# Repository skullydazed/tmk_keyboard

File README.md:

NOTICE: This repository is obsolete!
====================================

Please use my fork of QMK in the future: <https://github.com/skullydazed/qmk_firmware>

TMK Keyboard Firmware Collection
================================
This is a keyboard firmware with some useful features for Atmel AVR controller.

Source code is available here: <http://github.com/tmk/tmk_keyboard>

Updates
-------
#### 2015/04/22
Core library was separated to other branch `core`. <https://github.com/tmk/tmk_keyboard/tree/core>

In `Makefile` you need to set `TMK_DIR` to indicate core library location now.

    TMK_DIR = ../../tmk_core

Features
--------
These features can be used in your keyboard.

* Multi-layer Keymap  - Multiple keyboard layouts with layer switching
* Mouse key           - Mouse control with keyboard
* System Control Key  - Power Down, Sleep, Wake Up and USB Remote Wake up
* Media Control Key   - Volume Down/Up, Mute, Next/Prev track, Play, Stop and etc
* USB NKRO            - 120 keys(+ 8 modifiers) simultaneously
* PS/2 mouse support  - PS/2 mouse(TrackPoint) as composite device
* Keyboard protocols  - PS/2, ADB, M0110, Sun and other old keyboard protocols
* User Function       - Customizable function of key with writing code
* Macro               - Very primitive at this time
* Keyboard Tricks     - Oneshot modifier and modifier with tapping feature
* Debug Console       - Messages for debug and interaction with firmware
* Virtual DIP Switch  - Configurations stored EEPROM(Boot Magic)
* Locking CapsLock    - Mechanical switch support for CapsLock
* Breathing Sleep LED - Sleep indicator with charm during USB suspend
* Backlight           - Control backlight levels

Projects
--------
You can find some keyboard specific projects under `converter` and `keyboard` directory.

### converter
* [ps2_usb](converter/ps2_usb/)             - [PS/2 keyboard to USB][GH_ps2]
* [adb_usb](converter/adb_usb/)             - [ADB keyboard to USB][GH_adb]
* [m0110_usb](converter/m0110_usb)          - [Macintosh 128K/512K/Plus keyboard to USB][GH_m0110]
* [terminal_usb](converter/terminal_usb/)   - [IBM Model M terminal keyboard(PS/2 scancode set3) to USB][GH_terminal]
* [news_usb](converter/news_usb/)           - [Sony NEWS keyboard to USB][GH_news]
* [x68k_usb](converter/x68k_usb/)           - [Sharp X68000 keyboard to USB][GH_x68k]
* [sun_usb](converter/sun_usb/)             - [Sun] to USB(type4, 5 and 3?)
* [pc98_usb](converter/pc98_usb/)           - [PC98] to USB
* [usb_usb](converter/usb_usb/)             - USB to USB(experimental)
* [ascii_usb](converter/ascii_usb/)         - ASCII(Serial console terminal) to USB
* [ibm4704_usb](converter/ibm4704_usb)      - [IBM 4704 keyboard Converter][GH_ibm4704]

### keyboard
* [hhkb](keyboard/hhkb/)                    - [Happy Hacking Keyboard pro][GH_hhkb] **my main board**
* [gh60](keyboard/gh60/)                    - [GH60] DIY 60% keyboard [prototype][GH60_proto] **my second board**
* [hbkb](keyboard/hbkb/)                    - [Happy Buckling spring keyboard][GH_hbkb](IBM Model M 60% mod)
* [hid_liber](keyboard/hid_liber/)          - [HID liberation][HID_liber] controller (by alaricljs)
* [phantom](keyboard/phantom/)              - [Phantom] keyboard (by Tranquilite)
* [IIgs_Standard](keyboard/IIgs/)           - Apple [IIGS] keyboard mod(by JeffreySung)
* [macway](keyboard/macway/)                - [Compact keyboard mod][GH_macway] [retired]
* [KMAC](keyboard/kmac/)                    - Korean custom keyboard
* [Lightsaber](keyboard/lightsaber/)        - Korean custom keyboard
* [Infinity](keyboard/infinity/)            - Massdrop [Infinity keyboard][Infinity]
* [NerD](keyboard/nerd/)                    - Korean custom keyboard
* [KittenPaw](keyboard/kitten_paw)          - Custom Majestouch controller
* [Lightpad](keyboard/lightpad)             - Korean custom keypad
* [ghost_squid](keyboard/ghost_squid/)      - [The Ghost Squid][ghost_squid] controller for [Cooler Master QuickFire XT][cmxt]

### Extenal projects using tmk_keyboard
* [ErgoDox_cub-uanic][cub-uanic]            - Split Ergonomic Keyboard [ErgoDox][ergodox_org]
* [mcdox][mcdox_tmk]                        - [mcdox][mcdox]

[GH_macway]:    http://geekhack.org/showwiki.php?title=Island:11930
[GH_hhkb]:      http://geekhack.org/showwiki.php?title=Island:12047
[GH_ps2]:       http://geekhack.org/showwiki.php?title=Island:14618
[GH_adb]:       http://geekhack.org/showwiki.php?title=Island:14290
[GH_hhkb_bt]:   http://geekhack.org/showwiki.php?title=Island:20851
[GH_m0110]:     http://geekhack.org/showwiki.php?title=Island:24965
[GH_news]:      http://geekhack.org/showwiki.php?title=Island:25759
[GH_terminal]:  http://geekhack.org/showwiki.php?title=Island:27272
[GH_x68k]:      http://geekhack.org/showwiki.php?title=Island:29060
[GH_hbkb]:      http://geekhack.org/showwiki.php?title=Island:29483
[GH_ibm4704]:   http://geekhack.org/index.php?topic=54706.0
[HID_liber]:    http://deskthority.net/wiki/HID_Liberation_Device_-_DIY_Instructions
[Phantom]:      http://geekhack.org/index.php?topic=26742
[GH60]:         http://geekhack.org/index.php?topic=34959
[GH60_proto]:   http://geekhack.org/index.php?topic=37570.0
[PC98]:         http://en.wikipedia.org/wiki/NEC_PC-9801
[Sun]:          http://en.wikipedia.org/wiki/Sun-3
[IIGS]:         http://en.wikipedia.org/wiki/Apple_IIGS
[Infinity]:     https://www.massdrop.com/buy/infinity-keyboard-kit
[ghost_squid]:  http://deskthority.net/wiki/Costar_replacement_controllers#The_Ghost_Squid
[cmxt]:         http://gaming.coolermaster.com/en/products/keyboards/quickfirext/
[ergodox_org]:  http://ergodox.org/
[cub-uanic]:    https://github.com/cub-uanic/tmk_keyboard/tree/master/keyboard/ergodox
[mcdox]:        https://github.com/DavidMcEwan/mcdox
[mcdox_tmk]:    https://github.com/DavidMcEwan/tmk_keyboard/tree/master/keyboard/mcdox

License
-------
**GPLv2** or later. Some protocol files are under **Modified BSD License**.

Third party libraries like LUFA, PJRC and V-USB have their own license respectively.

Build Firmware and Program Controller
-------------------------------------
See [doc/build.md](doc/build.md).

Change your keymap
------------------
See [doc/keymap.md](doc/keymap.md).

Magic Commands
--------------
To see help press `Magic` + `H`.

`Magic` key combination is `LShift` + `RShift` in many project, but `Power` key on ADB converter. 
`Magic` keybind can be vary on each project, check `config.h` in project directory.

Following commands can be also executed with `Magic` + key. In console mode `Magic` keybind is not needed.

    ----- Command Help -----
    c:      enter console mode
    d:      toggle debug enable
    x:      toggle matrix debug
    k:      toggle keyboard debug
    m:      toggle mouse debug
    v:      print device version & info
    t:      print timer count
    s:      print status
    e:	    print eeprom config
    n:	    toggle NKRO
    0/F10:  switch to Layer0
    1/F1:   switch to Layer1
    2/F2:   switch to Layer2
    3/F3:   switch to Layer3
    4/F4:   switch to Layer4
    PScr:   power down/remote wake-up
    Caps:   Lock Keyboard(Child Proof)
    Paus:   jump to bootloader

Boot Magic Configuration - Virtual DIP Switch
---------------------------------------------
Boot Magic are executed during boot up time. Press Magic key below then plug in keyboard cable.
Note that you must use keys of **Layer 0** as Magic keys. These settings are stored in EEPROM so that retain your configure over power cycles.

To avoid configuring accidentally additive salt key `KC_SPACE` also needs to be pressed along with the following configuration keys. The salt key is configurable in `config.h`. See [tmk_core/common/bootmagic.h](tmk_core/common/bootmagic.h).

#### General
- Skip reading EEPROM to start with default configuration(`ESC`)
- Clear configuration stored in EEPROM to reset configuration(`Backspace`)

#### Bootloader
- Kick up Bootloader(`B`)

#### Debug
- Debug enable(`D`)
- Debug matrix enable(`D`+`X`)
- Debug keyboard enable(`D`+`K`)
- Debug mouse enable(`D`+`M`)

#### Keymap
- Swap Control and CapsLock(`Left Control`)
- Change CapsLock to Control(`Caps Lock`)
- Swap LeftAlt and Gui(`Left Alt`)
- Swap RightAlt and Gui(`Right Alt`)
- Disable Gui(`Left Gui`)
- Swap Grave and Escape(`Grave`)
- Swap BackSlash and BackSpace(`Back Slash`)
- Enable NKRO on boot(`N`)

#### Default Layer
- Set Default Layer to 0(`0`)
- Set Default Layer to 1(`1`)
- Set Default Layer to 2(`2`)
- Set Default Layer to 3(`3`)
- Set Default Layer to 4(`4`)
- Set Default Layer to 5(`5`)
- Set Default Layer to 6(`6`)
- Set Default Layer to 7(`7`)

Mechanical Locking support
--------------------------
This feature makes it possible for you to use mechanical locking switch for `CapsLock`, `NumLock` 
or `ScrollLock`. To enable this feature define these macros in `config.h` and use `KC_LCAP`, `KC_LN
UM` or `KC_LSCR` in keymap for locking key instead of normal `KC_CAPS`, `KC_NLCK` or `KC_SLCK`. Res
ync option tries to keep switch state consistent with keyboard LED state.
 
    #define LOCKING_SUPPORT_ENABLE
    #define LOCKING_RESYNC_ENABLE

Start Your Own Project
-----------------------
**TBD**

Debugging
--------
Use PJRC's `hid_listen` to see debug messages. You can use the tool for debug even if firmware use LUFA stack.

You can use xprintf() to display debug info on `hid_listen`, see `tmk_core/common/xprintf.h`.

Files and Directories
-------------------
### Top
* tmk_core/     - core library
* keyboard/     - keyboard projects
* converter/    - protocol converter projects
* doc/          - documents

Coding Style
-------------
- Doesn't use Tab to indent, use 4-spaces instead.

Other Keyboard Firmware Projects
------------------
You can learn a lot about keyboard firmware from these. See [doc/other_projects.md](doc/other_projects.md).

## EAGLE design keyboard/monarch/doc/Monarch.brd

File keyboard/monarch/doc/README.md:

Monarch keyboard firmware
=========================
DIY compact keyboard designed by koalapear, PCB designed by skullY.

## Monarch Resources
- [GeekHack Thread](https://geekhack.org/index.php?topic=75786.0)

## LED Support

After routing the matrix the Monarch had 2 pins left over. This allows for controllable lighting for two of the LED's. There are 3 possible LED's to turn on:

* Underlighting
* Capslock
* Numlock

There are two configurations available out of the box. You can switch between them by setting or commenting out the BACKLIGHT_ENABLE line in the Makefile. You must comment it out to disable it, changing it to NO will not work.

### Underlighting

To add underlighting to your Monarch you will need to solder on 16 SMD LED's and 16 matched resistors. For the LED's you can use anything from 0805 to 1206. If you have questions about whether your chosen LED/resistor combo will work post on the geekhack thread. Once you have added the components you will need to wire up the LED's.

There are 3 possible ways to wire underlighting:

* Always On
* Physical toggle switch
* Controllable brightness

To have your underlighting always on solder a jumper between GND and UNDERLIGHT, and another one between the FET bypass. This is the simplest way to enable underlighting.

If you would like to be able to turn off your underlighting, wire a physical toggle switch between the two contacts at the FET bypass.

To have controllable brightness connect C6 to UNDERLIGHT, and add a MOSFET and 10K resistor to the pads on the board. Make sure that the FET bypass is not connected. With BACKLIGHT_ENABLE set in the Makefile you can press Fn+Numlock to cycle through brightness levels.

### Capslock and Numlock

By default the firmware assumes you have CAPSLOCK wired to B6. If you have commented out BACKLIGHT_ENABLE it will assume that NUMLOCK is connected to C6. You can change this in [led.c](led.c).

## Build
Move to this directory then just run `make` like:

    $ make

## Keymap
Several version of keymap are available in advance but you are recommended to define your favorite layout yourself. To define your own keymap create file named `keymap_<name>.c` and see keymap document(you can find in top README.md) and existent keymap files.

To build firmware binary hex file with a certain keymap just do `make` with `KEYMAP` option like:

    $ make KEYMAP=[default|<name>]

### 1  default
[keymap_default.c](keymap_default.c) Default monarch layout

#### 1.0 Default ANSI layer
    FIXME

#### 1.1 Default Fn Layer
    FIXME

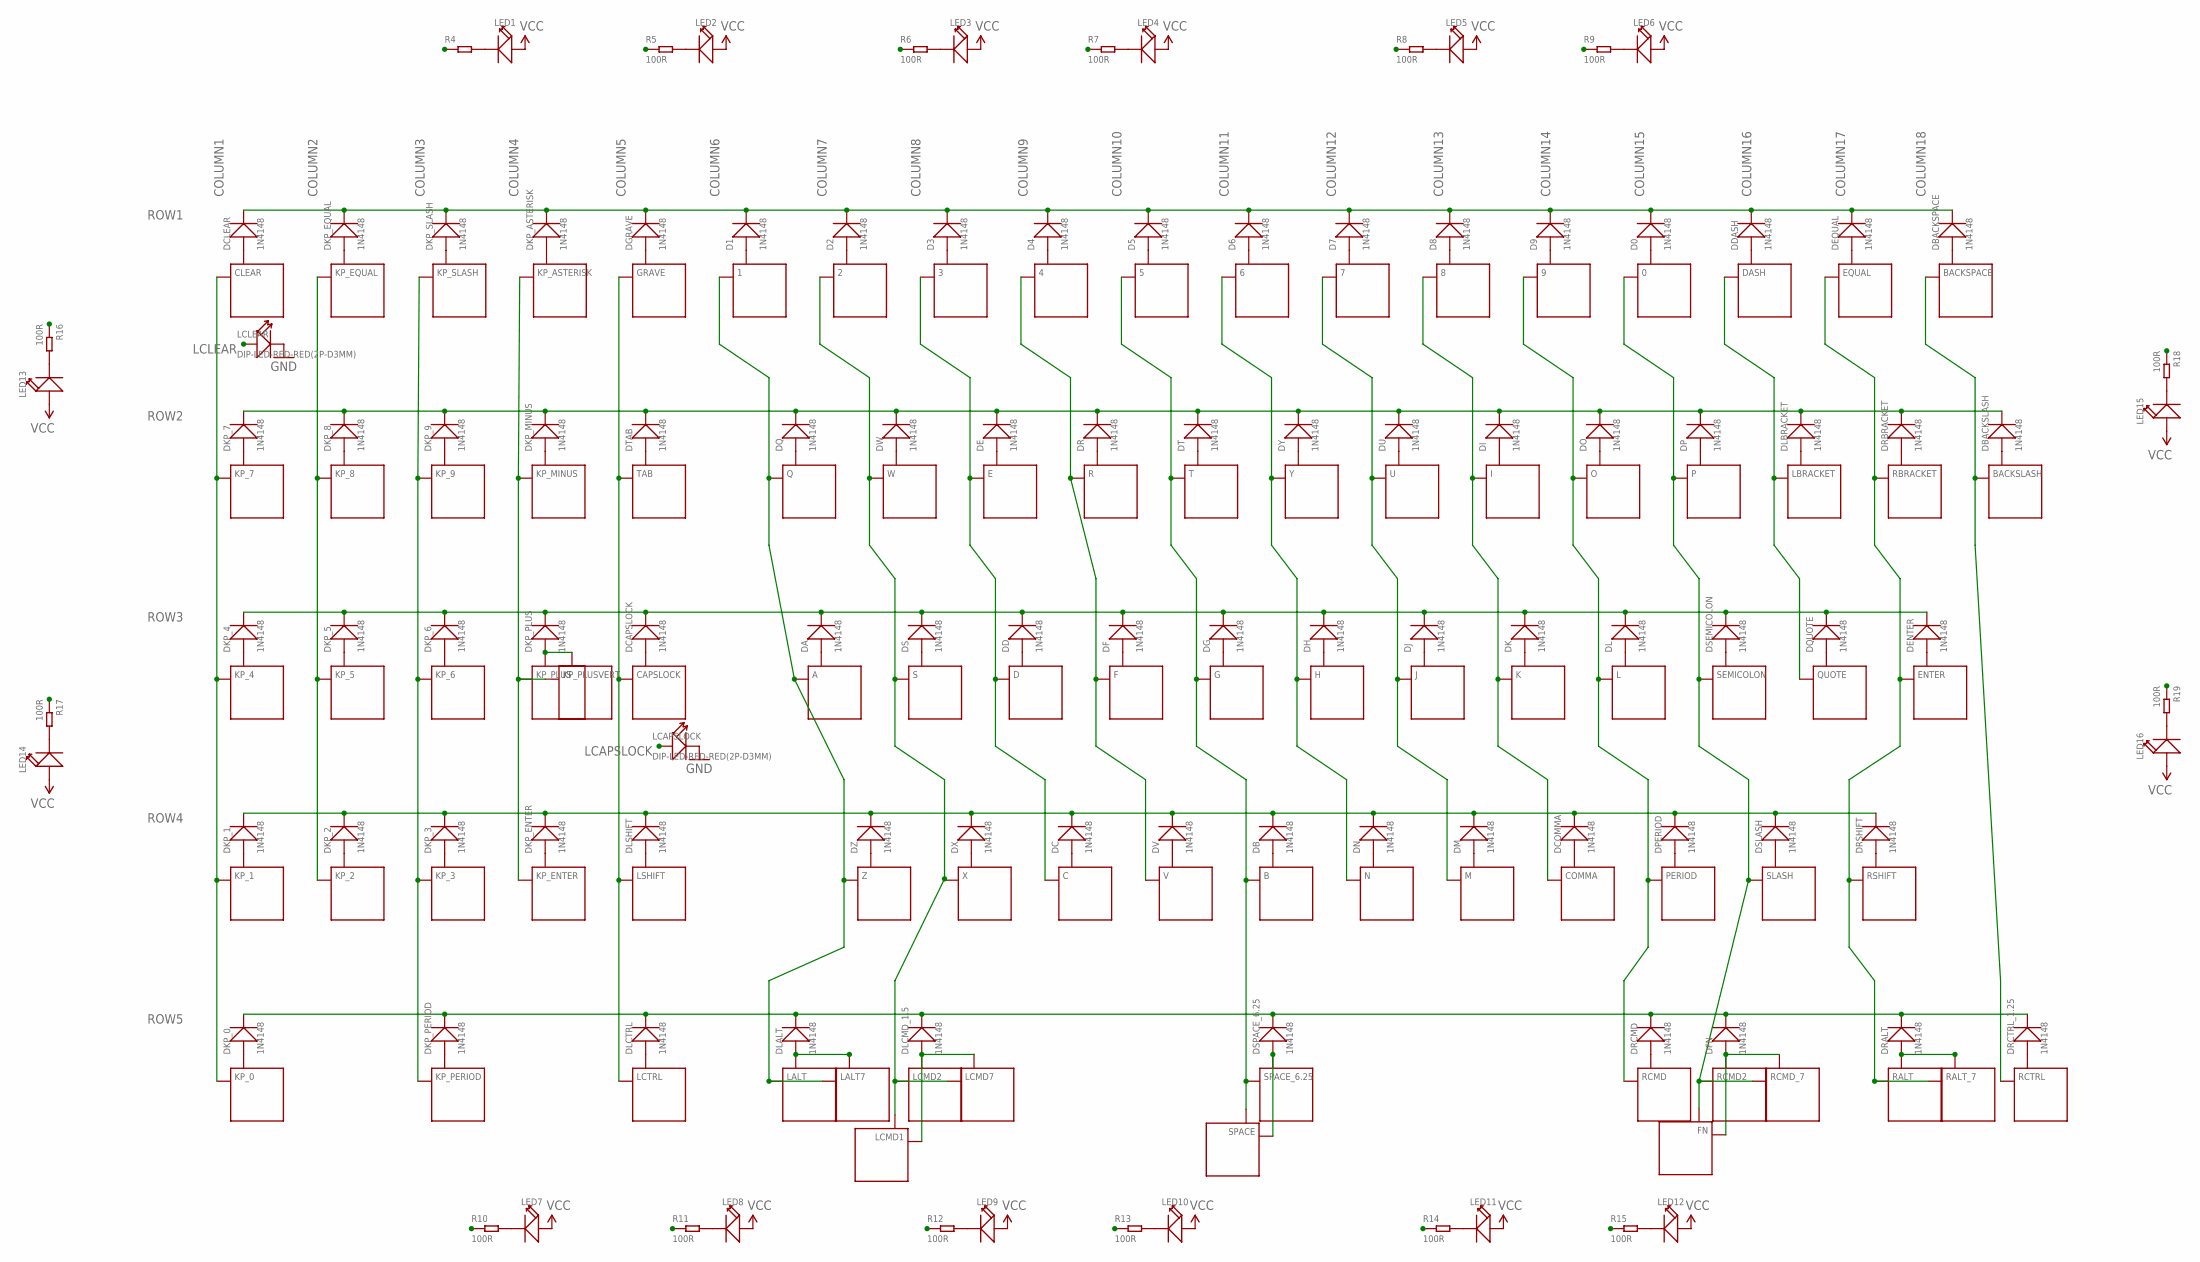
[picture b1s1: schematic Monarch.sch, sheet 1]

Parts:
0, 1, 2, 3, 4, 5, 6, 7, 8, 9: ALPS; P-ALPS
A: ALPS; P-ALPS
B: ALPS; P-ALPS
BACKSLASH: ALPS; P-ALPS
BACKSPACE: ALPS; P-ALPS
C: ALPS; P-ALPS
CAPSLOCK: ALPS; P-ALPS
CLEAR: ALPS; P-ALPS
COMMA: ALPS; P-ALPS
D: ALPS; P-ALPS
D0, D1, D2, D3, D4, D5, D6, D7, D8, D9: 1N4148; SOD-123
DA: 1N4148; SOD-123
DASH: ALPS; P-ALPS
DB: 1N4148; SOD-123
DBACKSLASH: 1N4148; SOD-123
DBACKSPACE: 1N4148; SOD-123
DC: 1N4148; SOD-123
DCAPSLOCK: 1N4148; SOD-123
DCLEAR: 1N4148; SOD-123
DCOMMA: 1N4148; SOD-123
DD: 1N4148; SOD-123
DDASH: 1N4148; SOD-123
DE: 1N4148; SOD-123
DENTER: 1N4148; SOD-123
DEQUAL: 1N4148; SOD-123
DF: 1N4148; SOD-123
DFN: 1N4148; SOD-123
DG: 1N4148; SOD-123
DGRAVE: 1N4148; SOD-123
DH: 1N4148; SOD-123
DI: 1N4148; SOD-123
DJ: 1N4148; SOD-123
DK: 1N4148; SOD-123
DKP_0, DKP_1, DKP_2, DKP_3, DKP_4, DKP_5, DKP_6, DKP_7, DKP_8, DKP_9: 1N4148; SOD-123
DKP_ASTERISK: 1N4148; SOD-123
DKP_ENTER: 1N4148; SOD-123
DKP_EQUAL: 1N4148; SOD-123
DKP_MINUS: 1N4148; SOD-123
DKP_PERIOD: 1N4148; SOD-123
DKP_PLUS: 1N4148; SOD-123
DKP_SLASH: 1N4148; SOD-123
DL: 1N4148; SOD-123
DLALT: 1N4148; SOD-123
DLBRACKET: 1N4148; SOD-123
DLCMD_1.5: 1N4148; SOD-123
DLCTRL: 1N4148; SOD-123
DLSHIFT: 1N4148; SOD-123
DM: 1N4148; SOD-123
DN: 1N4148; SOD-123
DO: 1N4148; SOD-123
DP: 1N4148; SOD-123
DPERIOD: 1N4148; SOD-123
DQ: 1N4148; SOD-123
DQUOTE: 1N4148; SOD-123
DR: 1N4148; SOD-123
DRALT: 1N4148; SOD-123
DRBRACKET: 1N4148; SOD-123
DRCMD: 1N4148; SOD-123
DRCTRL_1.25: 1N4148; SOD-123
DRSHIFT: 1N4148; SOD-123
DS: 1N4148; SOD-123
DSEMICOLON: 1N4148; SOD-123
DSLASH: 1N4148; SOD-123
DSPACE_6.25: 1N4148; SOD-123
DT: 1N4148; SOD-123
DTAB: 1N4148; SOD-123
DU: 1N4148; SOD-123
DV: 1N4148; SOD-123
DW: 1N4148; SOD-123
DX: 1N4148; SOD-123
DY: 1N4148; SOD-123
DZ: 1N4148; SOD-123
E: ALPS; P-ALPS
ENTER: ALPS; P-ALPS
EQUAL: ALPS; P-ALPS
F: ALPS; P-ALPS
FN: ALPS; P-ALPS
G: ALPS; P-ALPS
GRAVE: ALPS; P-ALPS
H: ALPS; P-ALPS
I: ALPS; P-ALPS
J: ALPS; P-ALPS
K: ALPS; P-ALPS
KP_0, KP_1, KP_2, KP_3, KP_4, KP_5, KP_6, KP_7, KP_8, KP_9: ALPS; P-ALPS
KP_ASTERISK: ALPS; P-ALPS
KP_ENTER: ALPS; P-ALPS
KP_EQUAL: ALPS; P-ALPS
KP_MINUS: ALPS; P-ALPS
KP_PERIOD: ALPS; P-ALPS
KP_PLUS: ALPS; P-ALPS
KP_PLUSVERT: ALPS; P-ALPS
KP_SLASH: ALPS; P-ALPS
L: ALPS; P-ALPS
LALT: ALPS-2SWITCH-0.5; P-ALPS-2SWITCH-0.5
LALT7: ALPS; P-ALPS
LBRACKET: ALPS; P-ALPS
LCAPSLOCK: DIP-LED-RED-RED(2P-D3MM); LED2-2.54-D3.0MM
LCLEAR: DIP-LED-RED-RED(2P-D3MM); LED2-2.54-D3.0MM
LCMD1, LCMD2, LCMD7: ALPS; P-ALPS
LCTRL: ALPS-2SWITCH-0.25; P-ALPS-2SWITCH-0.25
LED1, LED2, LED3, LED4, LED5, LED6, LED7, LED8, LED9, LED10, LED11, LED12, LED13, LED14, LED15, LED16: SMD-LED-GENERIC; P-SMD-LED-GENERIC
LSHIFT: ALPS; P-ALPS
M: ALPS; P-ALPS
N: ALPS; P-ALPS
O: ALPS; P-ALPS
P: ALPS; P-ALPS
PERIOD: ALPS; P-ALPS
Q: ALPS; P-ALPS
QUOTE: ALPS; P-ALPS
R: ALPS; P-ALPS
R4: SMD-RES-100R-5%-1/8W(0805); R0805
R5, R6, R7, R8, R9, R10, R11, R12, R13, R14, R15, R16, R17, R18, R19: 100R; R0805
RALT: ALPS-2SWITCH-0.5; P-ALPS-2SWITCH-0.5
RALT_7: ALPS; P-ALPS
RBRACKET: ALPS; P-ALPS
RCMD, RCMD2: ALPS; P-ALPS
RCMD_7: ALPS; P-ALPS
RCTRL: ALPS-2SWITCH-0.25; P-ALPS-2SWITCH-0.25
RSHIFT: ALPS; P-ALPS
S: ALPS; P-ALPS
SEMICOLON: ALPS; P-ALPS
SLASH: ALPS; P-ALPS
SPACE: ALPS; P-ALPS
SPACE_6.25: ALPS; P-ALPS
T: ALPS; P-ALPS
TAB: ALPS; P-ALPS
U: ALPS; P-ALPS
V: ALPS; P-ALPS
W: ALPS; P-ALPS
X: ALPS; P-ALPS
Y: ALPS; P-ALPS
Z: ALPS; P-ALPS

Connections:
COLUMN1: CLEAR.ALPS1, KP_0.ALPS1, KP_1.ALPS1, KP_4.ALPS1, KP_7.ALPS1; also elsewhere on the board
COLUMN2: KP_2.ALPS1, KP_5.ALPS1, KP_8.ALPS1, KP_EQUAL.ALPS1; also elsewhere on the board
COLUMN3: KP_3.ALPS1, KP_6.ALPS1, KP_9.ALPS1, KP_PERIOD.ALPS1, KP_SLASH.ALPS1; also elsewhere on the board
COLUMN4: KP_ASTERISK.ALPS1, KP_ENTER.ALPS1, KP_MINUS.ALPS1, KP_PLUS.ALPS1, KP_PLUSVERT.ALPS1; also elsewhere on the board
COLUMN5: CAPSLOCK.ALPS1, GRAVE.ALPS1, LCTRL.ALPS1, LCTRL.ALPS3, LSHIFT.ALPS1, TAB.ALPS1; also elsewhere on the board
COLUMN6: 1.ALPS1, A.ALPS1, LALT.ALPS1, LALT.ALPS4, LALT7.ALPS1, Q.ALPS1, Z.ALPS1; also elsewhere on the board
COLUMN7: 2.ALPS1, LCMD1.ALPS2, LCMD2.ALPS1, LCMD7.ALPS1, S.ALPS1, W.ALPS1, X.ALPS1; also elsewhere on the board
COLUMN8: 3.ALPS1, C.ALPS1, D.ALPS1, E.ALPS1; also elsewhere on the board
COLUMN9: 4.ALPS1, F.ALPS1, R.ALPS1, V.ALPS1; also elsewhere on the board
COLUMN10: 5.ALPS1, B.ALPS1, G.ALPS1, SPACE.ALPS2, SPACE_6.25.ALPS1, T.ALPS1; also elsewhere on the board
COLUMN11: 6.ALPS1, H.ALPS1, N.ALPS1, Y.ALPS1; also elsewhere on the board
COLUMN12: 7.ALPS1, J.ALPS1, M.ALPS1, U.ALPS1; also elsewhere on the board
COLUMN13: 8.ALPS1, COMMA.ALPS1, I.ALPS1, K.ALPS1; also elsewhere on the board
COLUMN14: 9.ALPS1, L.ALPS1, O.ALPS1, PERIOD.ALPS1, RCMD.ALPS1; also elsewhere on the board
COLUMN15: 0.ALPS1, FN.ALPS2, P.ALPS1, RCMD2.ALPS1, RCMD_7.ALPS1, SEMICOLON.ALPS1, SLASH.ALPS1; also elsewhere on the board
COLUMN16: DASH.ALPS1, LBRACKET.ALPS1, QUOTE.ALPS1; also elsewhere on the board
COLUMN17: ENTER.ALPS1, EQUAL.ALPS1, RALT.ALPS1, RALT.ALPS4, RALT_7.ALPS1, RBRACKET.ALPS1, RSHIFT.ALPS1; also elsewhere on the board
COLUMN18: BACKSLASH.ALPS1, BACKSPACE.ALPS1, RCTRL.ALPS1, RCTRL.ALPS3; also elsewhere on the board
GND: LCAPSLOCK.K (-), LCLEAR.K (-); also elsewhere on the board
LCAPSLOCK: LCAPSLOCK.A (+); also elsewhere on the board
LCLEAR: LCLEAR.A (+); also elsewhere on the board
unnamed: CLEAR.ALPS2, DCLEAR.+
unnamed: DKP_SLASH.+, KP_SLASH.ALPS2
unnamed: DKP_ASTERISK.+, KP_ASTERISK.ALPS2
unnamed: DKP_MINUS.+, KP_MINUS.ALPS2
unnamed: DGRAVE.+, GRAVE.ALPS2
unnamed: 1.ALPS2, D1.+
unnamed: 2.ALPS2, D2.+
unnamed: 3.ALPS2, D3.+
unnamed: 4.ALPS2, D4.+
unnamed: 5.ALPS2, D5.+
unnamed: 6.ALPS2, D6.+
unnamed: 7.ALPS2, D7.+
unnamed: 8.ALPS2, D8.+
unnamed: 9.ALPS2, D9.+
unnamed: 0.ALPS2, D0.+
unnamed: DASH.ALPS2, DDASH.+
unnamed: DEQUAL.+, EQUAL.ALPS2
unnamed: BACKSPACE.ALPS2, DBACKSPACE.+
unnamed: DKP_7.+, KP_7.ALPS2
unnamed: DKP_8.+, KP_8.ALPS2
unnamed: DKP_9.+, KP_9.ALPS2
unnamed: DKP_PLUS.+, KP_PLUS.ALPS2, KP_PLUSVERT.ALPS2
unnamed: DTAB.+, TAB.ALPS2
unnamed: DQ.+, Q.ALPS2
unnamed: DW.+, W.ALPS2
unnamed: DE.+, E.ALPS2
unnamed: DR.+, R.ALPS2
unnamed: DT.+, T.ALPS2
unnamed: DY.+, Y.ALPS2
unnamed: DU.+, U.ALPS2
unnamed: DI.+, I.ALPS2
unnamed: DO.+, O.ALPS2
unnamed: DP.+, P.ALPS2
unnamed: DLBRACKET.+, LBRACKET.ALPS2
unnamed: DRBRACKET.+, RBRACKET.ALPS2
unnamed: BACKSLASH.ALPS2, DBACKSLASH.+
unnamed: DKP_4.+, KP_4.ALPS2
unnamed: DKP_5.+, KP_5.ALPS2
unnamed: DKP_6.+, KP_6.ALPS2
unnamed: CAPSLOCK.ALPS2, DCAPSLOCK.+
unnamed: A.ALPS2, DA.+
unnamed: DS.+, S.ALPS2
unnamed: D.ALPS2, DD.+
unnamed: DF.+, F.ALPS2
unnamed: DG.+, G.ALPS2
unnamed: DH.+, H.ALPS2
unnamed: DJ.+, J.ALPS2
unnamed: DK.+, K.ALPS2
unnamed: DL.+, L.ALPS2
unnamed: DSEMICOLON.+, SEMICOLON.ALPS2
unnamed: DQUOTE.+, QUOTE.ALPS2
unnamed: DENTER.+, ENTER.ALPS2
unnamed: DKP_1.+, KP_1.ALPS2
unnamed: DKP_2.+, KP_2.ALPS2
unnamed: DKP_3.+, KP_3.ALPS2
unnamed: DKP_ENTER.+, KP_ENTER.ALPS2
unnamed: DLSHIFT.+, LSHIFT.ALPS2
unnamed: DZ.+, Z.ALPS2
unnamed: DX.+, X.ALPS2
unnamed: C.ALPS2, DC.+
unnamed: DV.+, V.ALPS2
unnamed: B.ALPS2, DB.+
unnamed: DN.+, N.ALPS2
unnamed: DM.+, M.ALPS2
unnamed: COMMA.ALPS2, DCOMMA.+
unnamed: DPERIOD.+, PERIOD.ALPS2
unnamed: DSLASH.+, SLASH.ALPS2
unnamed: DRSHIFT.+, RSHIFT.ALPS2
unnamed: DKP_0.+, KP_0.ALPS2
unnamed: DKP_PERIOD.+, KP_PERIOD.ALPS2
unnamed: DLCTRL.+, LCTRL.ALPS2, LCTRL.ALPS4
unnamed: DFN.+, FN.ALPS1, RCMD2.ALPS2, RCMD_7.ALPS2
unnamed: DKP_EQUAL.+, KP_EQUAL.ALPS2
unnamed: DLALT.+, LALT.ALPS2, LALT.ALPS3, LALT7.ALPS2
unnamed: DLCMD_1.5.+, LCMD1.ALPS1, LCMD2.ALPS2, LCMD7.ALPS2
unnamed: DSPACE_6.25.+, SPACE.ALPS1, SPACE_6.25.ALPS2
unnamed: DRCMD.+, RCMD.ALPS2
unnamed: DRALT.+, RALT.ALPS2, RALT.ALPS3, RALT_7.ALPS2
unnamed: DRCTRL_1.25.+, RCTRL.ALPS2, RCTRL.ALPS4
unnamed: LED1.MINUS, R4.2
unnamed: LED2.MINUS, R5.2
unnamed: LED3.MINUS, R6.2
unnamed: LED4.MINUS, R7.2
unnamed: LED5.MINUS, R8.2
unnamed: LED6.MINUS, R9.2
unnamed: LED15.MINUS, R18.2
unnamed: LED16.MINUS, R19.2
unnamed: LED12.MINUS, R15.2
unnamed: LED11.MINUS, R14.2
unnamed: LED10.MINUS, R13.2
unnamed: LED9.MINUS, R12.2
unnamed: LED8.MINUS, R11.2
unnamed: LED7.MINUS, R10.2
unnamed: LED14.MINUS, R17.2
unnamed: LED13.MINUS, R16.2
ROW1: D0.-, D1.-, D2.-, D3.-, D4.-, D5.-, D6.-, D7.-, D8.-, D9.-, DBACKSPACE.-, DCLEAR.-, DDASH.-, DEQUAL.-, DGRAVE.-, DKP_ASTERISK.-, DKP_EQUAL.-, DKP_SLASH.-; also elsewhere on the board
ROW2: DBACKSLASH.-, DE.-, DI.-, DKP_7.-, DKP_8.-, DKP_9.-, DKP_MINUS.-, DLBRACKET.-, DO.-, DP.-, DQ.-, DR.-, DRBRACKET.-, DT.-, DTAB.-, DU.-, DW.-, DY.-; also elsewhere on the board
ROW3: DA.-, DCAPSLOCK.-, DD.-, DENTER.-, DF.-, DG.-, DH.-, DJ.-, DK.-, DKP_4.-, DKP_5.-, DKP_6.-, DKP_PLUS.-, DL.-, DQUOTE.-, DS.-, DSEMICOLON.-; also elsewhere on the board
ROW4: DB.-, DC.-, DCOMMA.-, DKP_1.-, DKP_2.-, DKP_3.-, DKP_ENTER.-, DLSHIFT.-, DM.-, DN.-, DPERIOD.-, DRSHIFT.-, DSLASH.-, DV.-, DX.-, DZ.-; also elsewhere on the board
ROW5: DFN.-, DKP_0.-, DKP_PERIOD.-, DLALT.-, DLCMD_1.5.-, DLCTRL.-, DRALT.-, DRCMD.-, DRCTRL_1.25.-, DSPACE_6.25.-; also elsewhere on the board
UNDERLIGHT: R4.1, R5.1, R6.1, R7.1, R8.1, R9.1, R10.1, R11.1, R12.1, R13.1, R14.1, R15.1, R16.1, R17.1, R18.1, R19.1; also elsewhere on the board
VCC: LED1.PLUS, LED2.PLUS, LED3.PLUS, LED4.PLUS, LED5.PLUS, LED6.PLUS, LED7.PLUS, LED8.PLUS, LED9.PLUS, LED10.PLUS, LED11.PLUS, LED12.PLUS, LED13.PLUS, LED14.PLUS, LED15.PLUS, LED16.PLUS; also elsewhere on the board

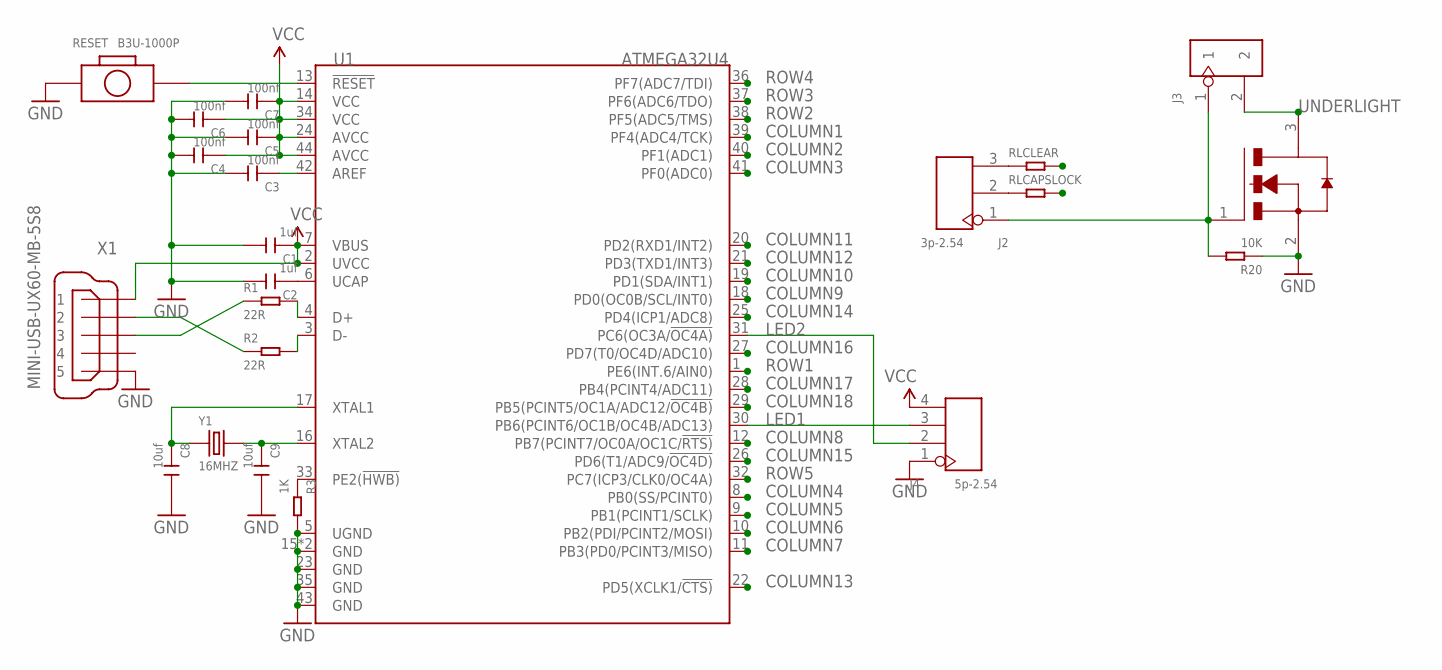
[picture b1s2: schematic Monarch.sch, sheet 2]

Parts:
C1, C2: 1uf; C0805
C3, C4, C5, C6, C7: 100nf; C0805
C8, C9: 10uf; C0805
FET1: MOSFET; SOT23
J2: 3p-2.54; H3-2.54
J3: DIP-BLACK-FEMALE-HEADER-VERT(2P-2.54); H2-2.54
J4: 5p-2.54; H4-2.54
R1, R2: 22R; R0805
R3: 1K; R0805
R20: 10K; R0805
RESET: B3U-1000P; SW2-SMD-3.0X2.5X1.2+0.4MM
RLCAPSLOCK: RES-0309/10; R0309_10
RLCLEAR: RES-0309/10; R0309_10
U1: ATMEGA32U4; QFN44G-0.5-7X7MM
X1: MINI-USB-UX60-MB-5S8; UX60-MB-5S8
Y1: 16MHZ; X2-SMD-5.0X3.2X1.3MM

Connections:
COLUMN1: U1.39 (PF4(ADC4/TCK)); also elsewhere on the board
COLUMN2: U1.40 (PF1(ADC1)); also elsewhere on the board
COLUMN3: U1.41 (PF0(ADC0)); also elsewhere on the board
COLUMN4: U1.8 (PB0(SS/PCINT0)); also elsewhere on the board
COLUMN5: U1.9 (PB1(PCINT1/SCLK)); also elsewhere on the board
COLUMN6: U1.10 (PB2(PDI/PCINT2/MOSI)); also elsewhere on the board
COLUMN7: U1.11 (PB3(PD0/PCINT3/MISO)); also elsewhere on the board
COLUMN8: U1.12 (PB7(PCINT7/OC0A/OC1C/!RTS)); also elsewhere on the board
COLUMN9: U1.18 (PD0(OC0B/SCL/INT0)); also elsewhere on the board
COLUMN10: U1.19 (PD1(SDA/INT1)); also elsewhere on the board
COLUMN11: U1.20 (PD2(RXD1/INT2)); also elsewhere on the board
COLUMN12: U1.21 (PD3(TXD1/INT3)); also elsewhere on the board
COLUMN13: U1.22 (PD5(XCLK1/!CTS)); also elsewhere on the board
COLUMN14: U1.25 (PD4(ICP1/ADC8)); also elsewhere on the board
COLUMN15: U1.26 (PD6(T1/ADC9/!OC4D)); also elsewhere on the board
COLUMN16: U1.27 (PD7(T0/OC4D/ADC10)); also elsewhere on the board
COLUMN17: U1.28 (PB4(PCINT4/ADC11)); also elsewhere on the board
COLUMN18: U1.29 (PB5(PCINT5/OC1A/ADC12/!OC4B)); also elsewhere on the board
GND: C1.2, C2.2, C3.2, C4.2, C5.2, C6.2, C7.2, C8.2, C9.2, FET1.2 (SOURCE), J4.1, R3.2, R20.1, RESET.1, U1.5 (UGND), U1.15 (GND), U1.23 (GND), U1.35 (GND), U1.43 (GND), U1.TAB (GND), X1.5; also elsewhere on the board
LCAPSLOCK: RLCAPSLOCK.2; also elsewhere on the board
LCLEAR: RLCLEAR.2; also elsewhere on the board
LED1: J4.3, U1.30 (PB6(PCINT6/OC1B/OC4B/ADC13))
LED2: J4.2, U1.31 (PC6(OC3A/!OC4A))
unnamed: R1.2, U1.4 (D+)
unnamed: R2.2, U1.3 (D-)
unnamed: C2.1, U1.6 (UCAP)
unnamed: C8.1, U1.17 (XTAL1), Y1.1
unnamed: C9.1, U1.16 (XTAL2), Y1.2
unnamed: R3.1, U1.33 (PE2(!HWB))
unnamed: C3.1, U1.42 (AREF)
unnamed: J2.2, RLCAPSLOCK.1
unnamed: R1.1, X1.3
unnamed: R2.1, X1.2
unnamed: J2.3, RLCLEAR.1
unnamed: FET1.1 (GATE), J2.1, J3.1, R20.2
RESET: RESET.2, U1.13 (!RESET)
ROW1: U1.1 (PE6(INT.6/AIN0)); also elsewhere on the board
ROW2: U1.38 (PF5(ADC5/TMS)); also elsewhere on the board
ROW3: U1.37 (PF6(ADC6/TDO)); also elsewhere on the board
ROW4: U1.36 (PF7(ADC7/TDI)); also elsewhere on the board
ROW5: U1.32 (PC7(ICP3/CLK0/OC4A)); also elsewhere on the board
UNDERLIGHT: FET1.3 (DRAIN), J3.2; also elsewhere on the board
VCC: C1.1, C4.1, C5.1, C6.1, C7.1, J4.4, U1.2 (UVCC), U1.7 (VBUS), U1.14 (VCC), U1.24 (AVCC), U1.34 (VCC), U1.44 (AVCC), X1.1; also elsewhere on the board

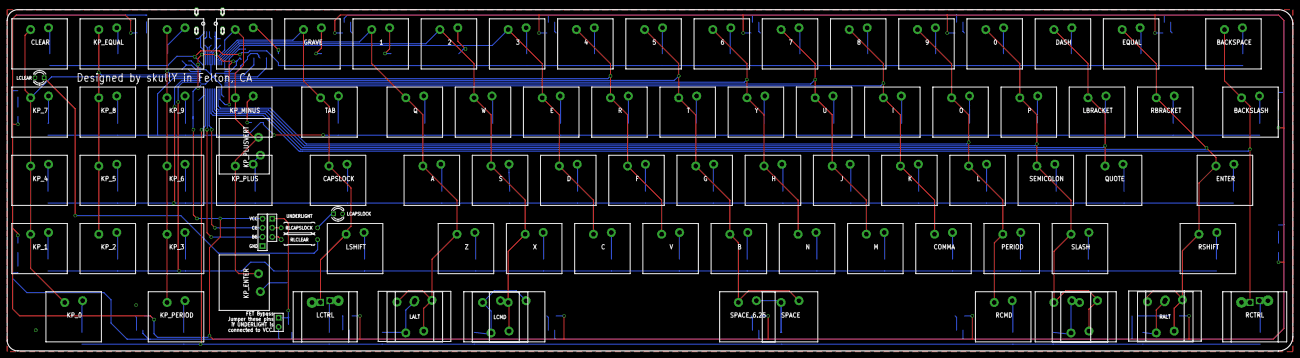
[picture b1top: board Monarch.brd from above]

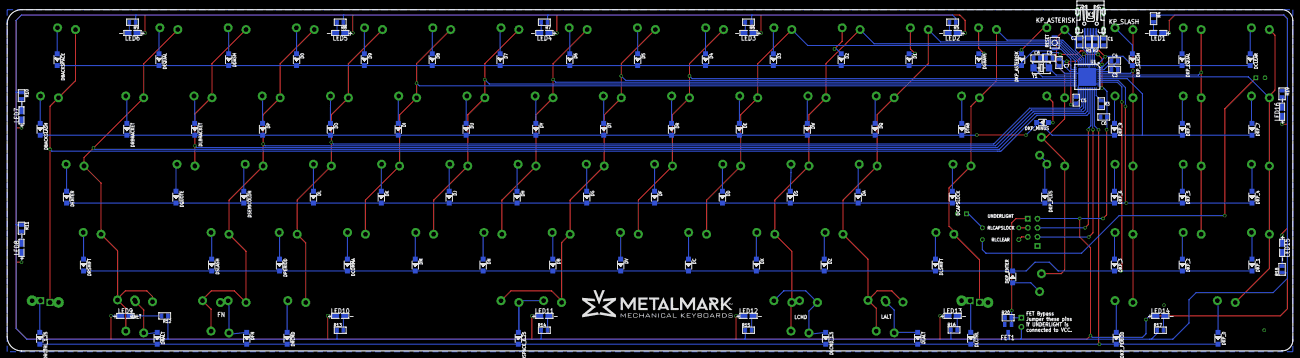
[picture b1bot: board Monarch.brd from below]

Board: 2 copper layers, 359.0 x 95.3 mm, 223 parts (129 on the bottom side), 138 nets.

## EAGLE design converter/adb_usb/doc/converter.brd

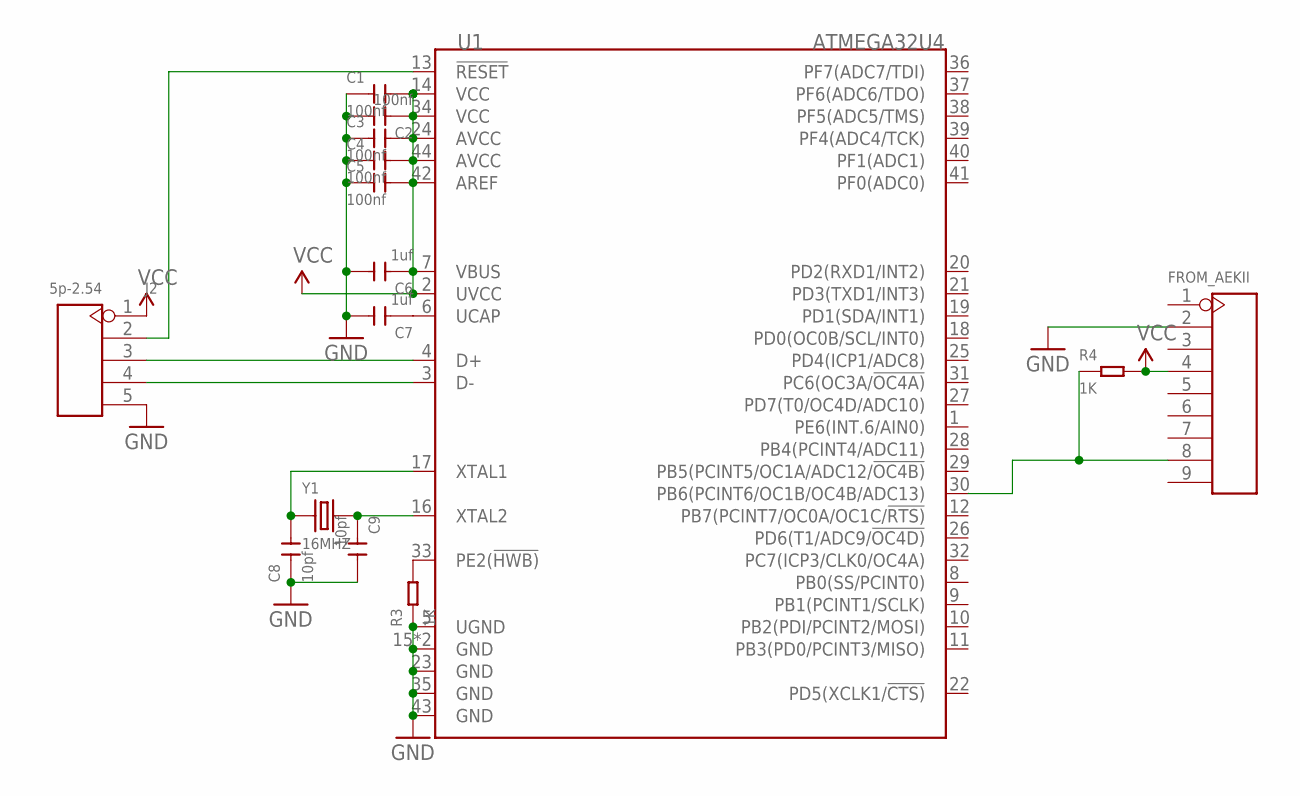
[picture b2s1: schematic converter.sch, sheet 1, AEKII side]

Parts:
C1, C2, C3, C4, C5: 100nf; C0603
C6, C7: 1uf; C0603
C8, C9: 10pf; C0603
FROM_AEKII: DIP-BLACK-FEMALE-HEADER-VERT(9P-2.0); H9-2.0
J2: 5p-2.54; H5-2.54
R3, R4: 1K; R0603
U1: ATMEGA32U4; QFN44G-0.5-7X7MM
Y1: 16MHZ; X2-SMD-5.0X3.2X1.3MM

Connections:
DATA: FROM_AEKII.8, R4.1, U1.30 (PB6(PCINT6/OC1B/OC4B/ADC13))
GND: C1.1, C2.2, C3.1, C4.1, C5.1, C6.2, C7.2, C8.1, C9.2, FROM_AEKII.2, J2.5, R3.1, U1.5 (UGND), U1.15 (GND), U1.23 (GND), U1.35 (GND), U1.43 (GND), U1.TAB (GND); also elsewhere on the board
unnamed: C7.1, U1.6 (UCAP)
unnamed: J2.3, U1.4 (D+)
unnamed: J2.4, U1.3 (D-)
unnamed: C8.2, U1.17 (XTAL1), Y1.1
unnamed: C9.1, U1.16 (XTAL2), Y1.2
unnamed: R3.2, U1.33 (PE2(!HWB))
RESET: J2.2, U1.13 (!RESET)
VCC: C1.2, C2.1, C3.2, C4.2, C5.2, C6.1, FROM_AEKII.4, J2.1, R4.2, U1.2 (UVCC), U1.7 (VBUS), U1.14 (VCC), U1.24 (AVCC), U1.34 (VCC), U1.42 (AREF), U1.44 (AVCC); also elsewhere on the board

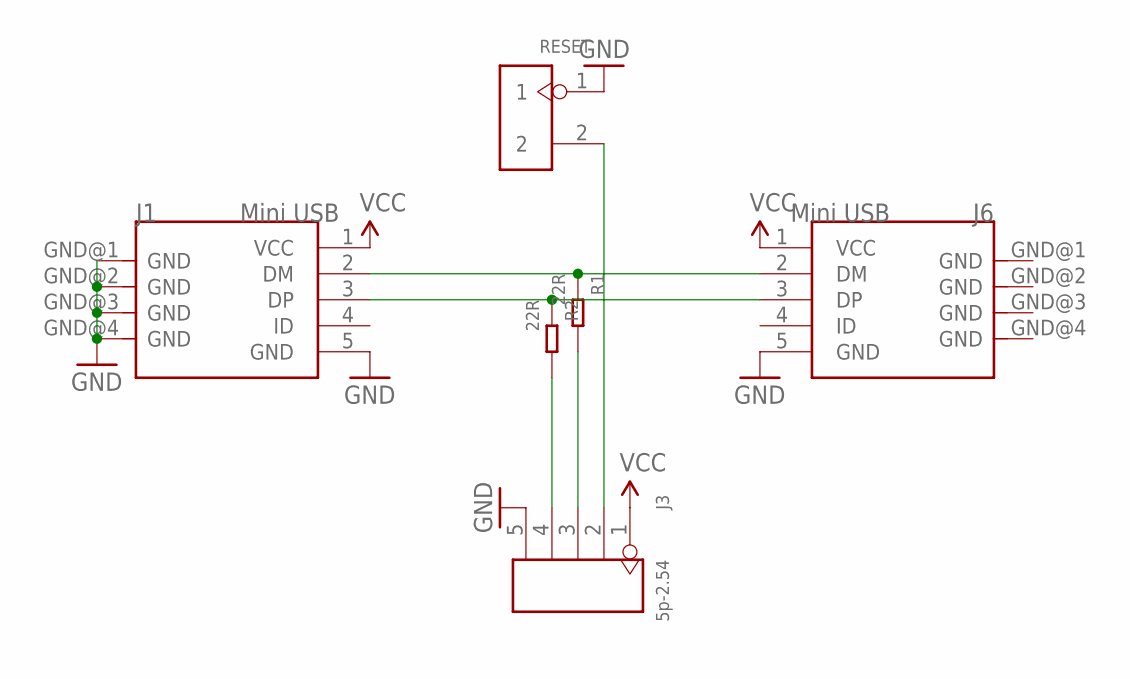
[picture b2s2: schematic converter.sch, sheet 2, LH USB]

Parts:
J1, J6: Mini USB; MINIUSB5+4P-0.8-90D
J3: 5p-2.54; H5-2.54
R1, R2: 22R; R0603
RESET: DIP-BLACK-FEMALE-HEADER-VERT(2P-2.54); H2-2.54

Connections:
GND: J1.5 (GND), J1.GND@1 (GND), J1.GND@2 (GND), J1.GND@3 (GND), J1.GND@4 (GND), J3.5, J6.5 (GND), RESET.1; also elsewhere on the board
unnamed: J3.2, RESET.2
unnamed: J3.3, R1.2
unnamed: J3.4, R2.2
USB_N: J1.2 (DM), J6.2 (DM), R1.1
USB_P: J1.3 (DP), J6.3 (DP), R2.1
VCC: J1.1 (VCC), J3.1, J6.1 (VCC); also elsewhere on the board

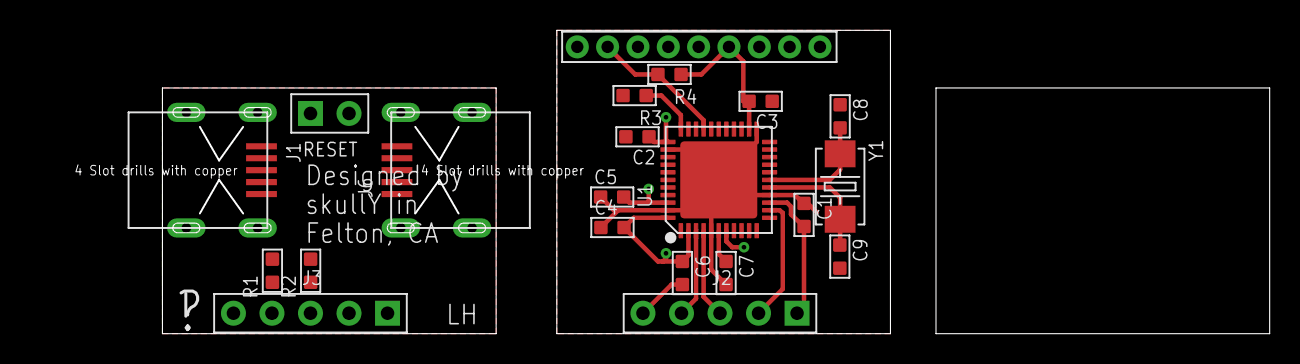
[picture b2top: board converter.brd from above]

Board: 2 copper layers, 73.0 x 20.0 mm, 21 parts (0 on the bottom side), 15 nets.

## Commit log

2015-07-21 Initial version of the CNC pad firmware
2015-07-24 Adding directory for my business card
2015-07-25 Change the pins over to the version 1.0 pins
2015-07-25 Rework the keymap to match the version 1.0 pcb
2015-07-25 Add a note on where to get the card
2015-09-09 Fix the rows/cols for cluecard
2015-09-09 First working cluecard firmware
2015-09-09 Add some experimental macro code
2015-09-09 Add code to turn on the rgb led
2015-09-10 Clueboard ADB Converter
2015-09-11 Fix #239 unresponsive keys of HHKB JP during power saving
2015-09-11 hhkb: Add power saving code of matrix scan for JP
2015-09-11 Fix 'enable break' commands for Alps models
    https://geekhack.org/index.php?topic=54706.msg1856618#msg1856618
2015-09-11 core: Fix lufa suspend callback(#234)
    With matrix_power_down() in suspend event HHKB JP doesn't start up for some reason.
    It is unneeded in actual and removed.
2015-09-12 Add code to turn on the led
2015-09-12 Working macro code
2015-09-12 Fix bug in macros
2015-09-13 Remove the unused fn1
2015-09-13 Fixup the adb_converter for my prototype hardware
2015-09-13 Make sure the clueboard works
2015-09-13 Source for the monarch keyboard firmware
2015-09-13 Adding schematic and layout documentation
2015-09-13 Add Ateml toolchain and remove specific chip name
2015-09-13 Fix parenthesis
2015-09-13 Fixup config.h for the monarch
2015-09-13 Adding documentation for version 1.1
2015-09-14 Update for the clueboard prototype
2015-09-14 Remove extraneous comment
2015-09-15 revert back to prototype's port
2015-09-23 Add layout for my personal keyboard
2015-10-04 Update the Monarch docs to revision 10 of the board
2015-10-14 Add a default layout for the clueboard
2015-10-26 Initial version of the TK78-R firmware
2015-10-26 clueboard -> tk78
2015-10-26 TK78-R: Setup the proper keymap and a single default layer
2015-11-05 Updating the monarch design files
2015-11-05 Latest default clueboard layout
2015-11-27 Setup a proper keymap for the monarch
2015-11-27 Remove the clueboard ascii art
2015-11-27 Update the monarch schematic and layout
2015-12-03 Tweak the default clueboard keymap
2015-12-03 Fix the 3edc column
2015-12-10 Add capslock/numlock support to the monarch
2015-12-10 Fix the tk78 firmware
2015-12-19 Initial support for the cluepad
2015-12-19 Add PWM support for backlighting.
2015-12-19 Fixup the readme
2015-12-19 Refactor the PWM setup
2015-12-20 Add underlight support to the monarch
2015-12-20 Add info on lighting to README.me
2015-12-20 Cluepad: Make numlock a dual function key
2016-01-16 Update build instructions for OSX
2016-01-24 Add a script for bulk keyboard loading
2016-03-29 Fixed qmk link
2016-04-09 Adding user keymaps
2016-04-09 Ignore .DS_Store files
2016-04-09 Update the tk78-r default keymap
2016-04-11 Add support for controlling the backlighting
2016-04-13 Fixup monarch LEDs
2016-04-17 Fix the underlight support for the monarch

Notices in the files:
converter/adb_usb/doc/converter.brd:
Copyright 2015
parts and their libraries:
SparkFun-Aesthetics: Licensing: Creative Commons ShareAlike 4.0 International - https://creativecommons.org/licenses/by-sa/4.0
